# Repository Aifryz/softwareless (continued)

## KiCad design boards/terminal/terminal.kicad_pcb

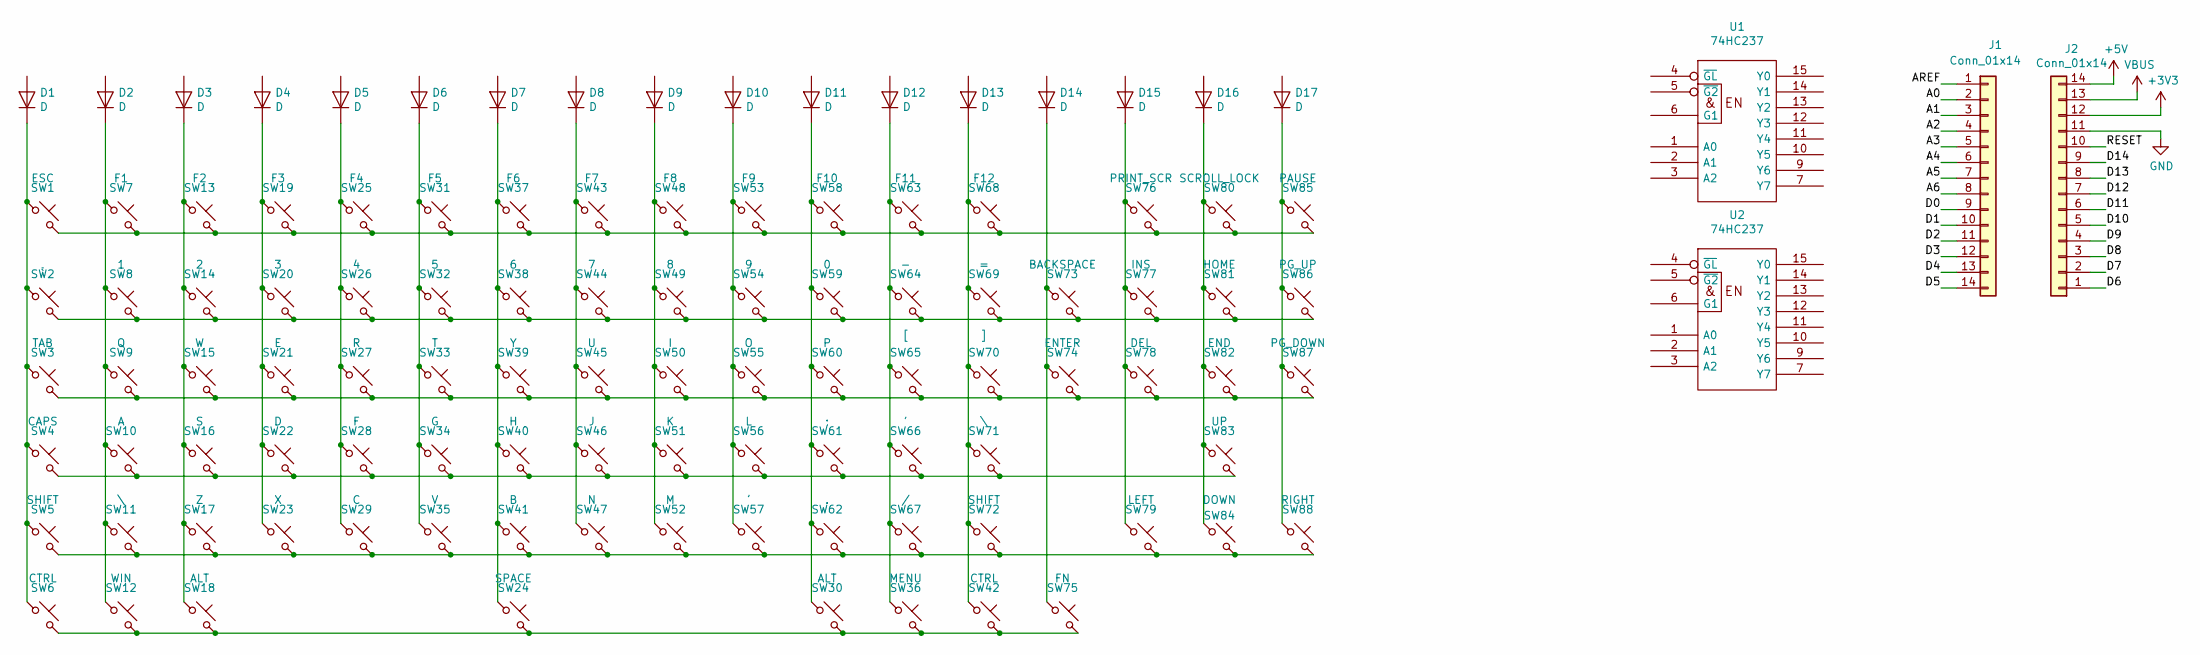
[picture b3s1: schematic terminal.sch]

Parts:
D1, D2, D3, D4, D5, D6, D7, D8, D9, D10, D11, D12, D13, D14, D15, D16, D17: D; D_SOD-323_HandSoldering
J1, J2: Conn_01x14; PinSocket_1x14_P2.54mm_Vertical
SW1: ESC; SW_Cherry_MX_1.00u_PCB
SW2: ~`; SW_Cherry_MX_1.00u_PCB
SW3: TAB; SW_Cherry_MX_1.50u_PCB
SW4: CAPS; SW_Cherry_MX_1.75u_PCB
SW5: SHIFT; SW_Cherry_MX_1.25u_PCB
SW6: CTRL; SW_Cherry_MX_1.50u_PCB
SW7: F1; SW_Cherry_MX_1.00u_PCB
SW8: 1; SW_Cherry_MX_1.00u_PCB
SW9: Q; SW_Cherry_MX_1.00u_PCB
SW10: A; SW_Cherry_MX_1.00u_PCB
SW11, SW71: \\; SW_Cherry_MX_1.00u_PCB
SW12: WIN; SW_Cherry_MX_1.25u_PCB
SW13: F2; SW_Cherry_MX_1.00u_PCB
SW14: 2; SW_Cherry_MX_1.00u_PCB
SW15: W; SW_Cherry_MX_1.00u_PCB
SW16: S; SW_Cherry_MX_1.00u_PCB
SW17: Z; SW_Cherry_MX_1.00u_PCB
SW18: ALT; SW_Cherry_MX_1.25u_PCB
SW19: F3; SW_Cherry_MX_1.00u_PCB
SW20: 3; SW_Cherry_MX_1.00u_PCB
SW21: E; SW_Cherry_MX_1.00u_PCB
SW22: D; SW_Cherry_MX_1.00u_PCB
SW23: X; SW_Cherry_MX_1.00u_PCB
SW24: SPACE; SW_Cherry_MX_6.25u_PCB
SW25: F4; SW_Cherry_MX_1.00u_PCB
SW26: 4; SW_Cherry_MX_1.00u_PCB
SW27: R; SW_Cherry_MX_1.00u_PCB
SW28: F; SW_Cherry_MX_1.00u_PCB
SW29: C; SW_Cherry_MX_1.00u_PCB
SW30: ALT; SW_Cherry_MX_1.50u_PCB
SW31: F5; SW_Cherry_MX_1.00u_PCB
SW32: 5; SW_Cherry_MX_1.00u_PCB
SW33: T; SW_Cherry_MX_1.00u_PCB
SW34: G; SW_Cherry_MX_1.00u_PCB
SW35: V; SW_Cherry_MX_1.00u_PCB
SW36: MENU; SW_Cherry_MX_1.50u_PCB
SW37: F6; SW_Cherry_MX_1.00u_PCB
SW38: 6; SW_Cherry_MX_1.00u_PCB
SW39: Y; SW_Cherry_MX_1.00u_PCB
SW40: H; SW_Cherry_MX_1.00u_PCB
SW41: B; SW_Cherry_MX_1.00u_PCB
SW42: CTRL; SW_Cherry_MX_1.00u_PCB
SW43: F7; SW_Cherry_MX_1.00u_PCB
SW44: 7; SW_Cherry_MX_1.00u_PCB
SW45: U; SW_Cherry_MX_1.00u_PCB
SW46: J; SW_Cherry_MX_1.00u_PCB
SW47: N; SW_Cherry_MX_1.00u_PCB
SW48: F8; SW_Cherry_MX_1.00u_PCB
SW49: 8; SW_Cherry_MX_1.00u_PCB
SW50: I; SW_Cherry_MX_1.00u_PCB
SW51: K; SW_Cherry_MX_1.00u_PCB
SW52: M; SW_Cherry_MX_1.00u_PCB
SW53: F9; SW_Cherry_MX_1.00u_PCB
SW54: 9; SW_Cherry_MX_1.00u_PCB
SW55: O; SW_Cherry_MX_1.00u_PCB
SW56: L; SW_Cherry_MX_1.00u_PCB
SW57: ,; SW_Cherry_MX_1.00u_PCB
SW58: F10; SW_Cherry_MX_1.00u_PCB
SW59: 0; SW_Cherry_MX_1.00u_PCB
SW60: P; SW_Cherry_MX_1.00u_PCB
SW61: ;; SW_Cherry_MX_1.00u_PCB
SW62: .; SW_Cherry_MX_1.00u_PCB
SW63: F11; SW_Cherry_MX_1.00u_PCB
SW64: -; SW_Cherry_MX_1.00u_PCB
SW65: [; SW_Cherry_MX_1.00u_PCB
SW66: '; SW_Cherry_MX_1.00u_PCB
SW67: /; SW_Cherry_MX_1.00u_PCB
SW68: F12; SW_Cherry_MX_1.00u_PCB
SW69: =; SW_Cherry_MX_1.00u_PCB
SW70: ]; SW_Cherry_MX_1.00u_PCB
SW72: SHIFT; SW_Cherry_MX_2.75u_PCB
SW73: BACKSPACE; SW_Cherry_MX_2.00u_PCB
SW74: ENTER; SW_Cherry_MX_ISOEnter_PCB
SW75: FN; SW_Cherry_MX_1.00u_PCB
SW76: PRINT_SCR; SW_Cherry_MX_1.00u_PCB
SW77: INS; SW_Cherry_MX_1.00u_PCB
SW78: DEL; SW_Cherry_MX_1.00u_PCB
SW79: LEFT; SW_Cherry_MX_1.00u_PCB
SW80: SCROLL_LOCK; SW_Cherry_MX_1.00u_PCB
SW81: HOME; SW_Cherry_MX_1.00u_PCB
SW82: END; SW_Cherry_MX_1.00u_PCB
SW83: UP; SW_Cherry_MX_1.00u_PCB
SW84: DOWN; SW_Cherry_MX_1.00u_PCB
SW85: PAUSE; SW_Cherry_MX_1.00u_PCB
SW86: PG_UP; SW_Cherry_MX_1.00u_PCB
SW87: PG_DOWN; SW_Cherry_MX_1.00u_PCB
SW88: RIGHT; SW_Cherry_MX_1.00u_PCB
U1, U2: 74HC237; SOIC-16_3.9x9.9mm_P1.27mm

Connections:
+3V3: J2.12
+5V: J2.14
/A0: J1.2
/A1: J1.3
/A2: J1.4
/A3: J1.5
/A4: J1.6
/A5: J1.7
/A6: J1.8
/AREF: J1.1
/D0: J1.9
/D1: J1.10
/D2: J1.11
/D3: J1.12
/D4: J1.13
/D5: J1.14
/D6: J2.1
/D7: J2.2
/D8: J2.3
/D9: J2.4
/D10: J2.5
/D11: J2.6
/D12: J2.7
/D13: J2.8
/D14: J2.9
/RESET: J2.10
GND: J2.11, U1.8 (GND), U2.8 (GND)
unnamed: D1.1 (K), SW1.1, SW2.1, SW3.1, SW4.1, SW5.1, SW6.1
unnamed: D2.1 (K), SW7.1, SW8.1, SW9.1, SW10.1, SW11.1, SW12.1
unnamed: D3.1 (K), SW13.1, SW14.1, SW15.1, SW16.1, SW17.1, SW18.1
unnamed: D4.1 (K), SW19.1, SW20.1, SW21.1, SW22.1, SW23.1
unnamed: D5.1 (K), SW25.1, SW26.1, SW27.1, SW28.1, SW29.1
unnamed: D6.1 (K), SW31.1, SW32.1, SW33.1, SW34.1, SW35.1
unnamed: D7.1 (K), SW24.1, SW37.1, SW38.1, SW39.1, SW40.1, SW41.1
unnamed: D8.1 (K), SW43.1, SW44.1, SW45.1, SW46.1, SW47.1
unnamed: D9.1 (K), SW48.1, SW49.1, SW50.1, SW51.1, SW52.1
unnamed: D10.1 (K), SW53.1, SW54.1, SW55.1, SW56.1, SW57.1
unnamed: D11.1 (K), SW30.1, SW58.1, SW59.1, SW60.1, SW61.1, SW62.1
unnamed: D12.1 (K), SW36.1, SW63.1, SW64.1, SW65.1, SW66.1, SW67.1
unnamed: D13.1 (K), SW42.1, SW68.1, SW69.1, SW70.1, SW71.1, SW72.1
unnamed: D14.1 (K), SW73.1, SW74.1, SW75.1
unnamed: D15.1 (K), SW76.1, SW77.1, SW78.1, SW79.1
unnamed: D16.1 (K), SW80.1, SW81.1, SW82.1, SW83.1, SW84.1
unnamed: D17.1 (K), SW85.1, SW86.1, SW87.1, SW88.1
unnamed: SW1.2, SW7.2, SW13.2, SW19.2, SW25.2, SW31.2, SW37.2, SW43.2, SW48.2, SW53.2, SW58.2, SW63.2, SW68.2, SW76.2, SW80.2, SW85.2
unnamed: SW4.2, SW10.2, SW16.2, SW22.2, SW28.2, SW34.2, SW40.2, SW46.2, SW51.2, SW56.2, SW61.2, SW66.2, SW71.2, SW83.2
unnamed: SW5.2, SW11.2, SW17.2, SW23.2, SW29.2, SW35.2, SW41.2, SW47.2, SW52.2, SW57.2, SW62.2, SW67.2, SW72.2, SW79.2, SW84.2, SW88.2
unnamed: SW6.2, SW12.2, SW18.2, SW24.2, SW30.2, SW36.2, SW42.2, SW75.2
unnamed: SW2.2, SW8.2, SW14.2, SW20.2, SW26.2, SW32.2, SW38.2, SW44.2, SW49.2, SW54.2, SW59.2, SW64.2, SW69.2, SW73.2, SW77.2, SW81.2, SW86.2
unnamed: SW3.2, SW9.2, SW15.2, SW21.2, SW27.2, SW33.2, SW39.2, SW45.2, SW50.2, SW55.2, SW60.2, SW65.2, SW70.2, SW74.2, SW78.2, SW82.2, SW87.2
VBUS: J2.13
VCC: U1.16 (VCC), U2.16 (VCC)

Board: 2 copper layers, 109 parts (0 on the bottom side), 25 nets, no tracks yet.

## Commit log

2021-11-25 Added some cpu files
2022-01-11 Add initial terminal schematic and switch layout
2022-01-14 Fix keyboard layout
2022-01-14 Added script to make keyboard position setting less painfull
2022-01-30 Add ALU files
2022-02-05 Remove some bugs in ALU, add shifts
2022-02-08 Add partialy tested fetch unit
2022-02-12 Some fetch fixes
2022-02-13 Rename terminal to keyboard
2022-02-19 Add LED display files
2022-03-05 Add partial led board layout
2022-03-19 Update schematics
2022-03-19 Add logo
2022-05-08 Add production files, fix licensing
2022-05-08 Add logo to readme
2022-05-08 Fix logo size
2022-05-22 Start adding decompression
2022-05-29 Add not tested decompress functionality
2022-05-29 Add test vector for decompress
2024-03-31 Minimally working CPU
2024-05-14 Add some branch support
2024-05-16 Removed separate control module
2024-06-05 Added jumps and rets
2025-02-02 Add file driven decompress tests
2025-02-12 Fix decode issues
